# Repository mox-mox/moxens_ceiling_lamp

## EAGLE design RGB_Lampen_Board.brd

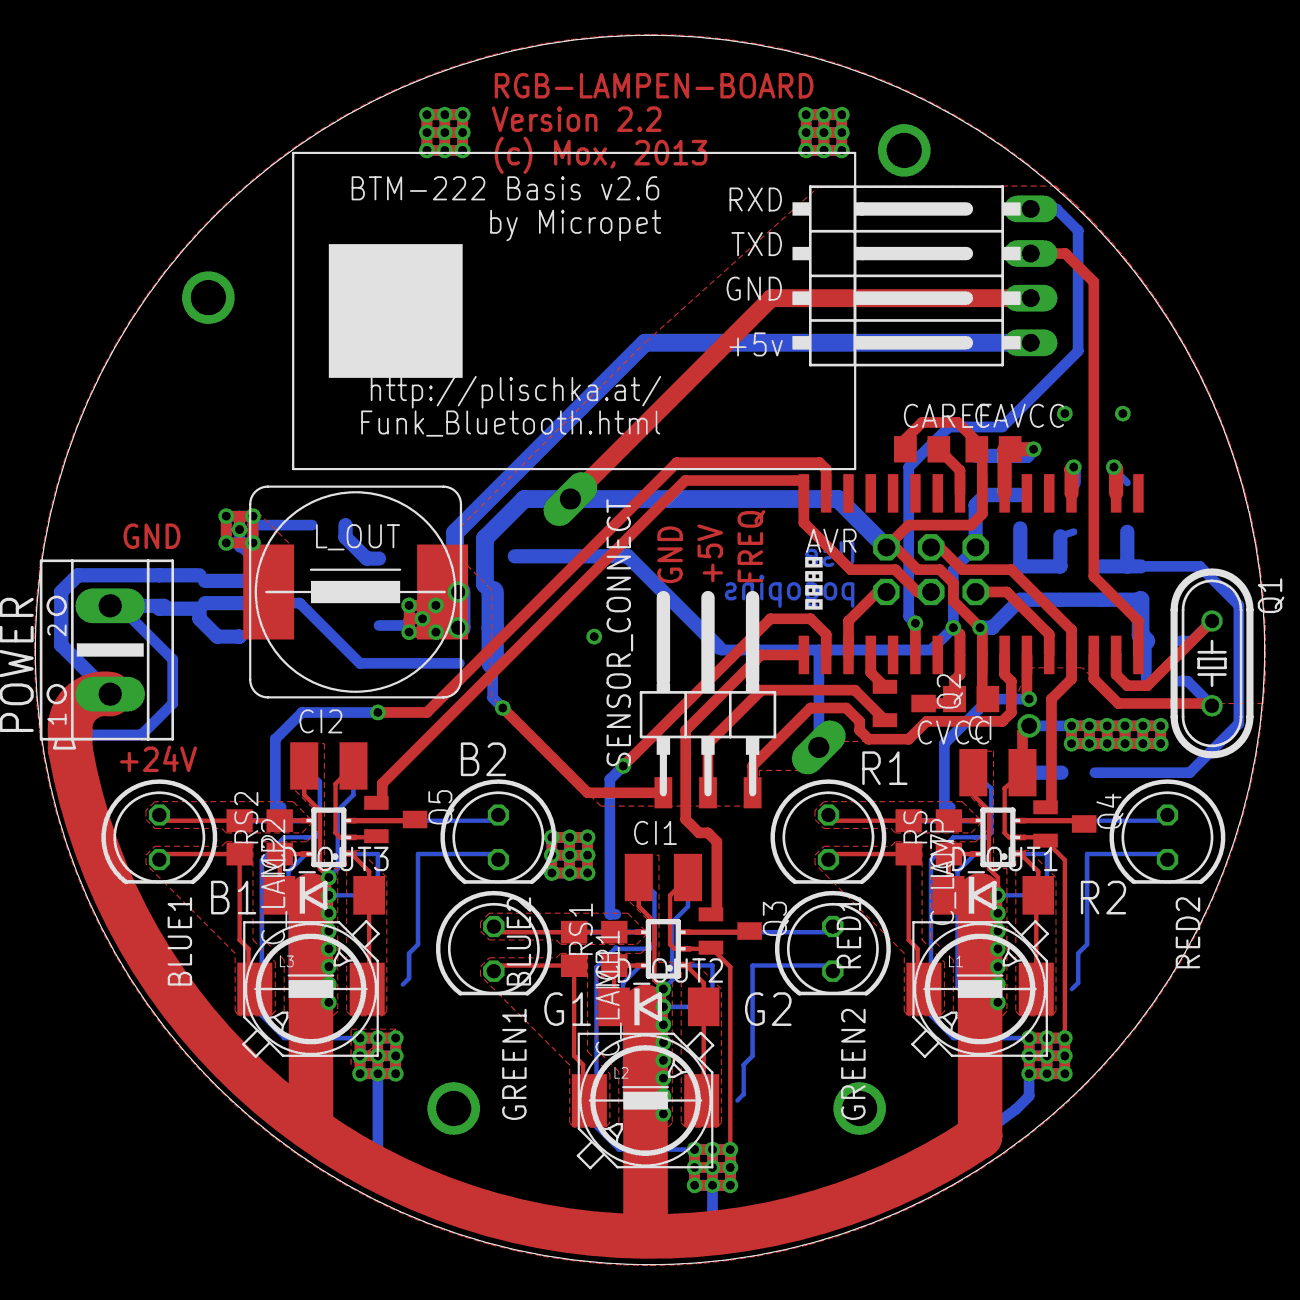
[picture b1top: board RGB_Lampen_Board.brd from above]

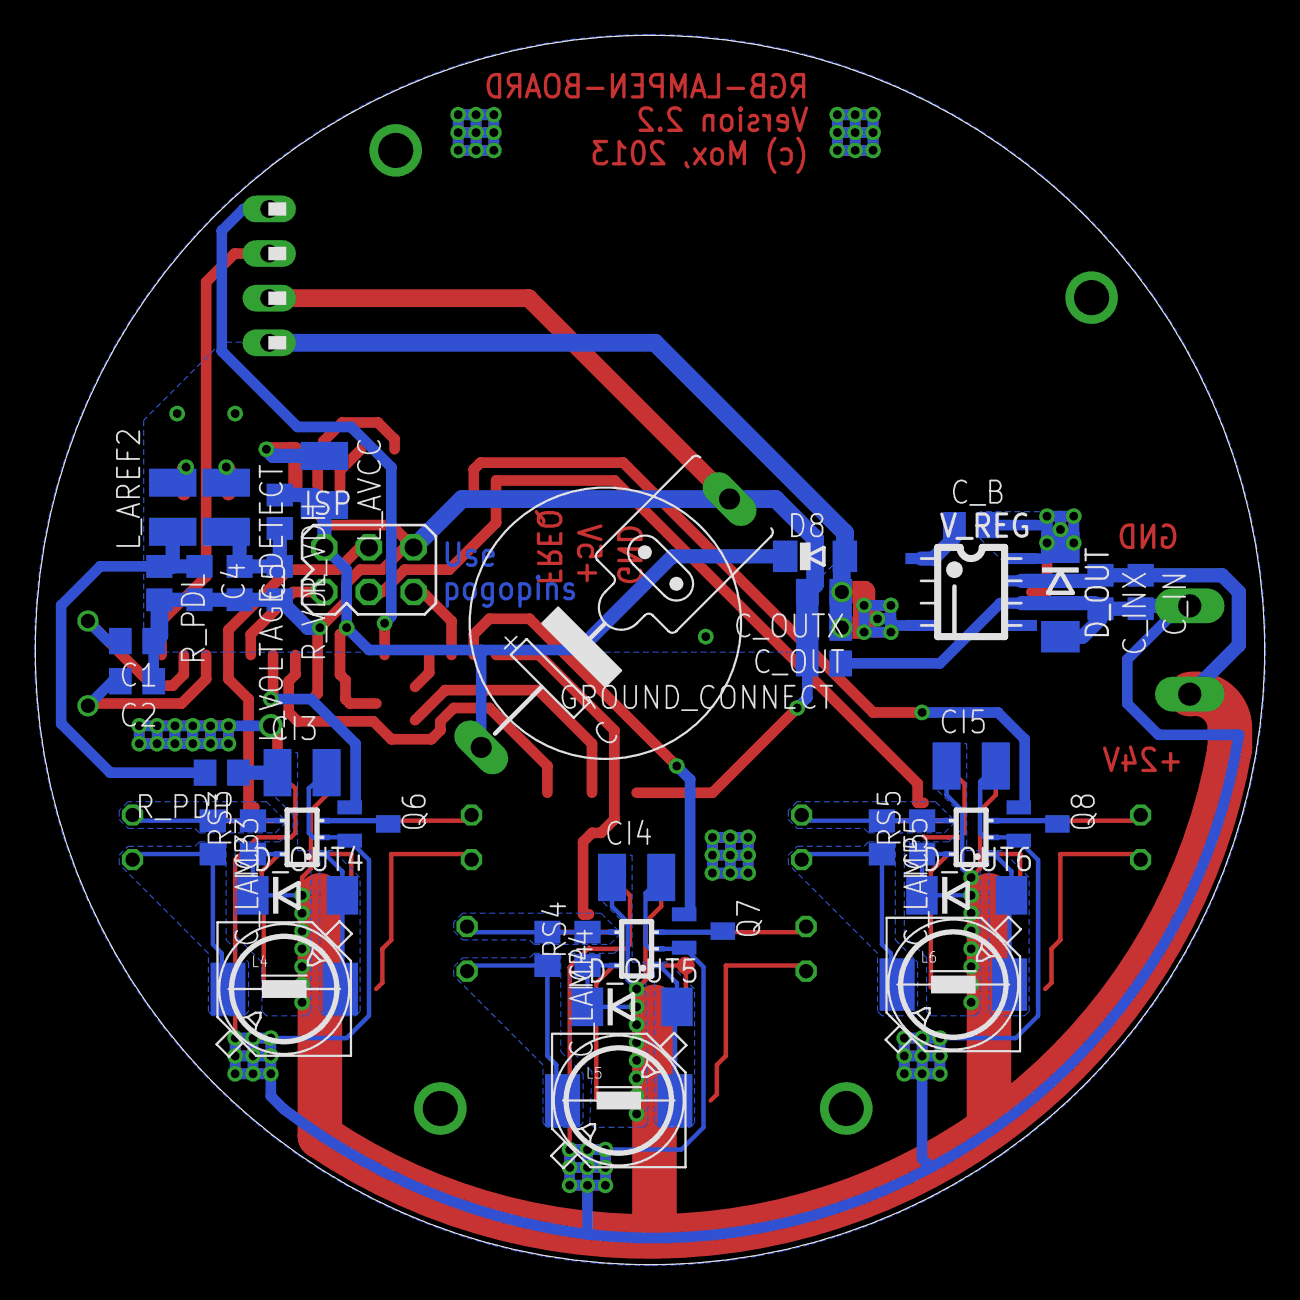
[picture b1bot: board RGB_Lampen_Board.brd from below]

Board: 2 copper layers, 70.0 x 70.0 mm, 81 parts (43 on the bottom side), 52 nets.

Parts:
AVR: AT90PWM3B_NO_PIN_19NO_PIN_19; SO32W_NO_PIN_19
BLUE1, BLUE2: 350mA/18,0..21.6V; LED5MM
C: 1F/5.5V; PANASONIC_SG_TERMINAL_H
C1, C2: 30pF; C0805
C4, C5: 100nF; C0805
CAREF: 100nF; C0805
CAVCC: 100nF; C0805
CI, CI1, CI2, CI3, CI4, CI5: 10µF/50V; C1210
CVCC: 100nF; C0805
C_B: 10nF; C0805
C_IN: 1µF/50V; C0805
C_INX: 100nF/50V; C0805
C_LAMP, C_LAMP1, C_LAMP2, C_LAMP3, C_LAMP4, C_LAMP5: 1µF; C0805
C_OUT: 10µF/25V; C0805
C_OUTX: 100nF; C0805
D8: BAS86-GS08; MINIMELF
D_OUT, D_OUT1, D_OUT2, D_OUT3, D_OUT4, D_OUT5, D_OUT6: SK16; DO214AA
GREEN1, GREEN2: 350mA/18,0..21.6V; LED5MM
GROUND_CONNECT: 0 Ohm; R0805
IC1, IC2, IC3, IC4, IC5, IC7: ZXLD1360; TSOT23-5
L1, L2, L3, L4, L5, L6: 100µF; FERROCORE_DER0705-
L_AREF2: 10µH; L1210
L_AVCC: 10µH; L1210
L_OUT: 470µH; FERROCORE_DE1207-
L_VOLTAGE_DETECT: 10µH; L1210
POWER: 24V/2.5A; AK500/2
Q1: 16MHz; HC49/S
Q2: AP2305BGN-HF-3; SOT23
Q3, Q4, Q5, Q6, Q7, Q8: IRLML2502GPbF; SOT23
RED1, RED2: 350mA/12,0..15.6V; LED5MM
RS, RS1, RS2, RS3, RS4, RS5: 286m; R0805
R_PDH: 51k; R0805
R_PDL: 10k; R0805
R_VDH: 80k; R0805
R_VDL: 10k; R0805
SENSOR_CONNECT: 1X03SMD/90
U$1: BTM-222-BASIS; BTM-222
U$3: LP_NUMBER_SILK_TOP
U$7: AVR-ISPTHT; AVR-ISP-THT
V_REG: LM2675M; SO08

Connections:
+5V: C_OUT.1, C_OUTX.1, D8.A, L_OUT.P$2, U$1.+5V, V_REG.4
+24V: CI.1, CI1.1, CI2.1, CI3.1, CI4.1, CI5.1, C_IN.1, C_INX.1, D_OUT1.C, D_OUT2.C, D_OUT3.C, D_OUT4.C, D_OUT5.C, D_OUT6.C, IC1.5, IC2.5, IC3.5, IC4.5, IC5.5, IC7.5, POWER.1, RS.1, RS1.1, RS2.1, RS3.1, RS4.1, RS5.1, R_PDH.1, V_REG.7
AGND: CI.2, CI1.2, CI2.2, CI3.2, CI4.2, CI5.2, C_IN.2, C_INX.2, D_OUT.A, GROUND_CONNECT.1, IC1.2, IC2.2, IC3.2, IC4.2, IC5.2, IC7.2, POWER.2, Q3.2, Q4.2, Q5.2, Q6.2, Q7.2, Q8.2, V_REG.6
AREF: AVR.25, CAREF.2
AVCC: AVR.23, CAVCC.2, L_AVCC.1
B1_SCK: AVR.32, Q5.1, U$7.3
B2: AVR.31, Q8.1
FREQ_IN: AVR.10, SENSOR_CONNECT.3
G1: AVR.1, Q3.1
G2: AVR.2, Q7.1
GND: AVR.9, AVR.24, C.-, C1.1, C2.1, C4.2, C5.2, CAREF.1, CAVCC.1, CVCC.1, C_OUT.2, C_OUTX.2, GROUND_CONNECT.2, R_PDL.2, R_VDL.2, SENSOR_CONNECT.1, U$1.GND, U$7.6
MISO: AVR.12, U$7.1
unnamed: AVR.20, L_VOLTAGE_DETECT.1
unnamed: C_LAMP.1, IC7.4, RED1.A, RS.2
unnamed: C_LAMP.2, L1.P$1, RED1.K
unnamed: D_OUT2.A, IC1.1, L2.P$2
unnamed: IC1.3, Q3.3
unnamed: C_LAMP1.2, GREEN1.K, L2.P$1
unnamed: C_LAMP1.1, GREEN1.A, IC1.4, RS1.2
unnamed: D_OUT3.A, IC2.1, L3.P$2
unnamed: IC2.3, Q5.3
unnamed: BLUE1.K, C_LAMP2.2, L3.P$1
unnamed: BLUE1.A, C_LAMP2.1, IC2.4, RS2.2
unnamed: D_OUT4.A, IC3.1, L4.P$2
unnamed: IC3.3, Q6.3
unnamed: C_LAMP3.2, L4.P$1, RED2.K
unnamed: IC7.3, Q4.3
unnamed: D_OUT1.A, IC7.1, L1.P$2
unnamed: C_LAMP3.1, IC3.4, RED2.A, RS3.2
unnamed: D_OUT5.A, IC4.1, L5.P$2
unnamed: IC4.3, Q7.3
unnamed: C_LAMP4.2, GREEN2.K, L5.P$1
unnamed: C_LAMP4.1, GREEN2.A, IC4.4, RS4.2
unnamed: D_OUT6.A, IC5.1, L6.P$2
unnamed: C_B.1, V_REG.1
unnamed: IC5.3, Q8.3
unnamed: BLUE2.K, C_LAMP5.2, L6.P$1
unnamed: BLUE2.A, C_LAMP5.1, IC5.4, RS5.2
unnamed: AVR.14, C2.2, Q1.2
unnamed: AVR.15, C1.2, Q1.1
unnamed: Q2.2, SENSOR_CONNECT.2
POWER_DETECT: C4.1, L_AREF2.1, R_PDH.2, R_PDL.1
POWER_DETECT_: AVR.18, L_AREF2.2
R1_MOSI: AVR.13, Q4.1, U$7.4
R2: AVR.11, Q6.1
RESET: AVR.3, U$7.5
RXD: AVR.16, U$1.TXD
SWITCH: C_B.2, D_OUT.C, L_OUT.P$1, V_REG.8
S_PWR: AVR.4, Q2.1
TXD: AVR.6, U$1.RXD
V+: AVR.8, C.+, CVCC.2, D8.C, L_AVCC.2, Q2.3, R_VDH.1, U$7.2
VOLTAGE_DETECT: C5.1, L_VOLTAGE_DETECT.2, R_VDH.2, R_VDL.1

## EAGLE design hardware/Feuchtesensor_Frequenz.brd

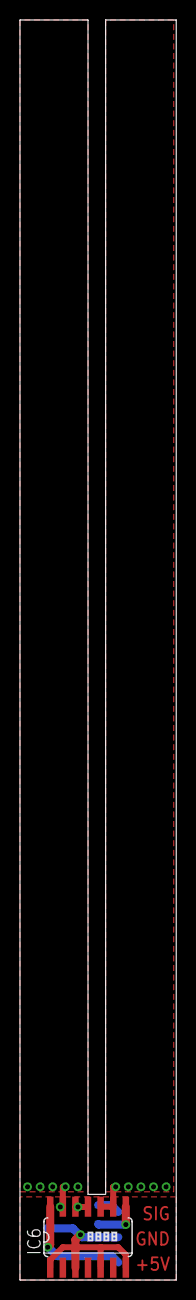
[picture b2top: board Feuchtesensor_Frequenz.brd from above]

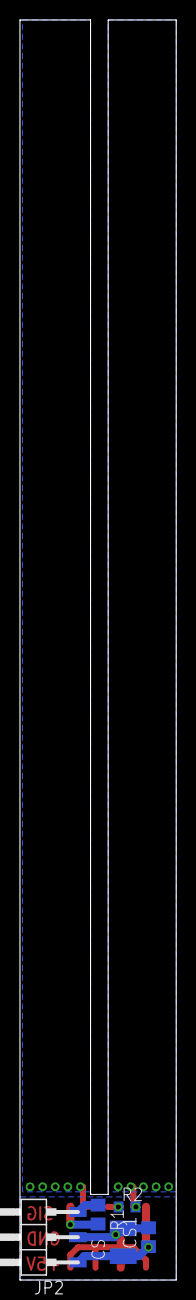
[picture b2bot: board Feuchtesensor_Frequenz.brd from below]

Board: 2 copper layers, 15.7 x 127.0 mm, 7 parts (5 on the bottom side), 7 nets.

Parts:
CS: 10µF/50V; C1210
CS1: 100nF/50V; C0805
IC6: 74HC14D; SO14
JP2: 1X03SMD/90
R1: 100; R0805
R2: ca 100k; R0603
U$2: LP_NUMBER_SILK_TOP

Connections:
GNDA: CS.2, CS1.2, IC6.1, IC6.3, IC6.5, IC6.7, JP2.2
unnamed: IC6.13, R2.2
unnamed: IC6.11, IC6.12, R2.1
unnamed: IC6.9, IC6.10
SIG: JP2.3, R1.1
SIG_: IC6.8, R1.2
VCC: CS.1, CS1.1, IC6.14, JP2.1
